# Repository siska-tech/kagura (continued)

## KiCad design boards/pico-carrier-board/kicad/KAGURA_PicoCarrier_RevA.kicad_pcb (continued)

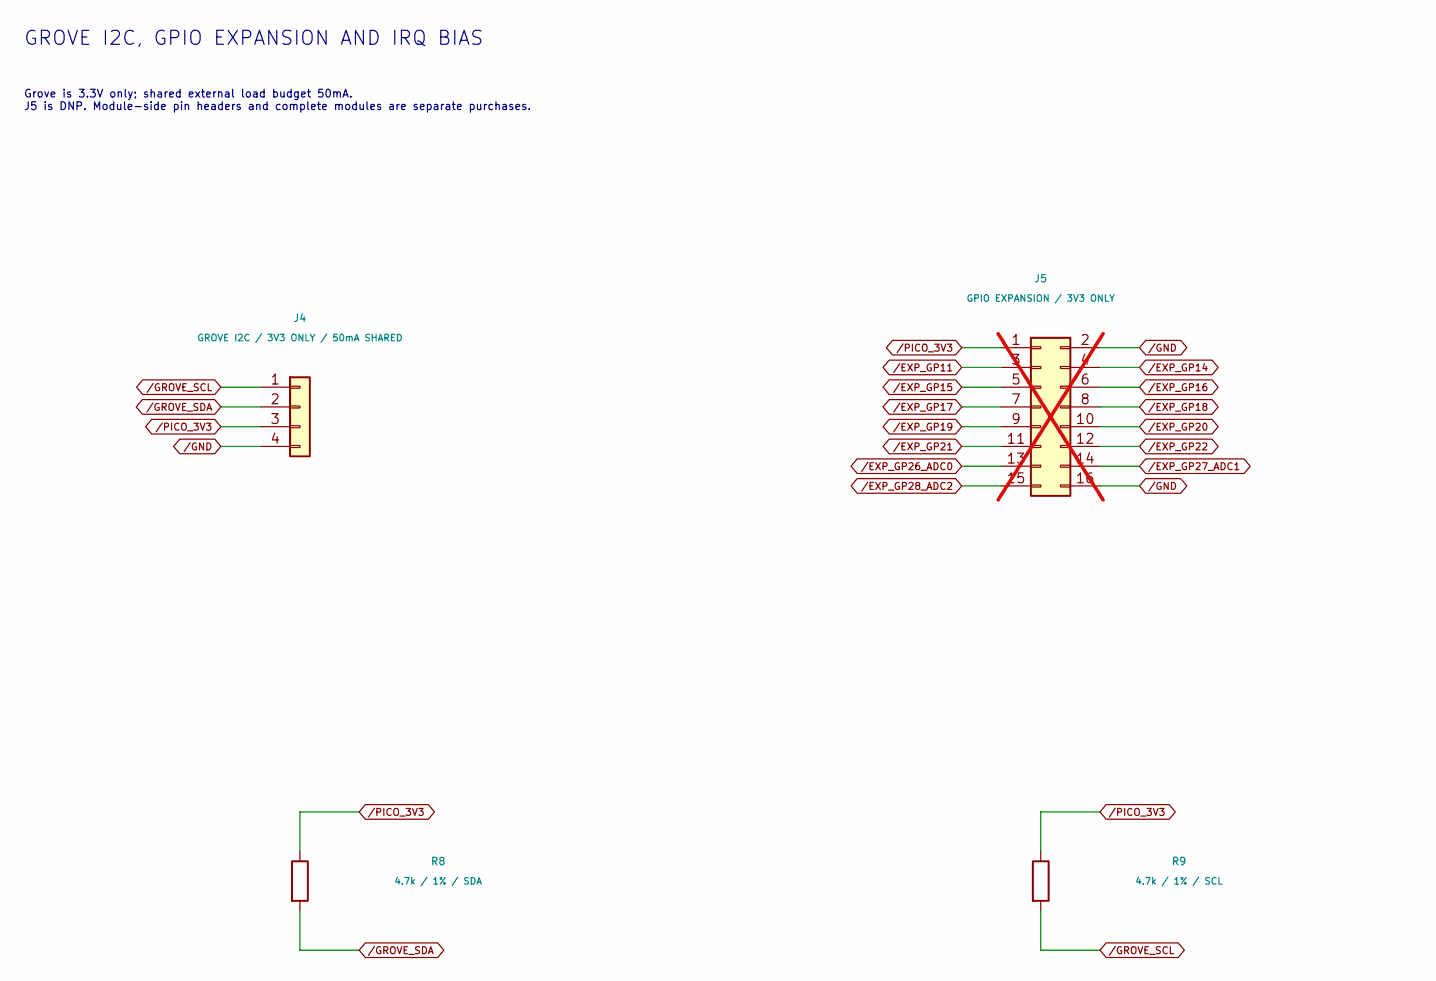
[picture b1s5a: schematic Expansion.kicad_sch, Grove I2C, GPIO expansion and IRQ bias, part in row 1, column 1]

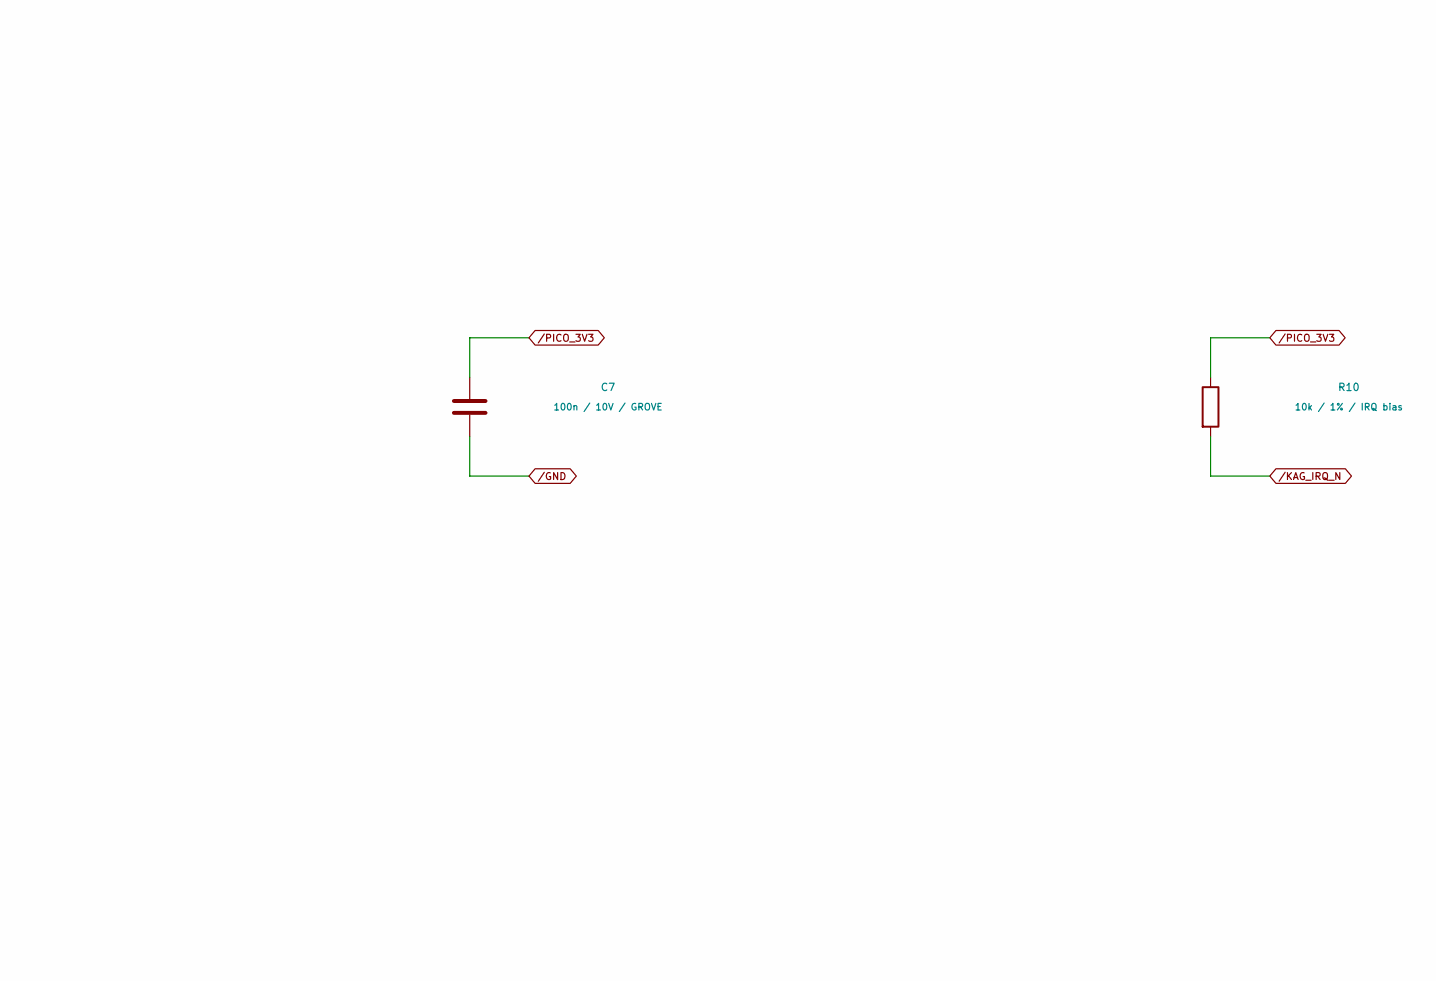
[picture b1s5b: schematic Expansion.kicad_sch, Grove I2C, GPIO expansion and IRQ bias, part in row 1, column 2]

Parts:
C7: 100n / 10V / GROVE; C7
J4: GROVE I2C / 3V3 ONLY / 50mA SHARED; J4
J5: GPIO EXPANSION / 3V3 ONLY; J5; not fitted
R8: 4.7k / 1% / SDA; R8
R9: 4.7k / 1% / SCL; R9
R10: 10k / 1% / IRQ bias; R10

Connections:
/EXP_GP11: J5.3; also elsewhere on the board
/EXP_GP14: J5.4; also elsewhere on the board
/EXP_GP15: J5.5; also elsewhere on the board
/EXP_GP16: J5.6; also elsewhere on the board
/EXP_GP17: J5.7; also elsewhere on the board
/EXP_GP18: J5.8; also elsewhere on the board
/EXP_GP19: J5.9; also elsewhere on the board
/EXP_GP20: J5.10; also elsewhere on the board
/EXP_GP21: J5.11; also elsewhere on the board
/EXP_GP22: J5.12; also elsewhere on the board
/EXP_GP26_ADC0: J5.13; also elsewhere on the board
/EXP_GP27_ADC1: J5.14; also elsewhere on the board
/EXP_GP28_ADC2: J5.15; also elsewhere on the board
/GND: C7.2, J4.4, J5.2, J5.16; also elsewhere on the board
/GROVE_SCL: J4.1, R9.2; also elsewhere on the board
/GROVE_SDA: J4.2, R8.2; also elsewhere on the board
/KAG_IRQ_N: R10.2; also elsewhere on the board
/PICO_3V3: C7.1, J4.3, J5.1, R8.1, R9.1, R10.1; also elsewhere on the board

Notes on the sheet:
GROVE I2C, GPIO EXPANSION AND IRQ BIAS
Grove is 3.3V only; shared external load budget 50mA. J5 is DNP. Module-side pin headers and complete modules are separate purchases.

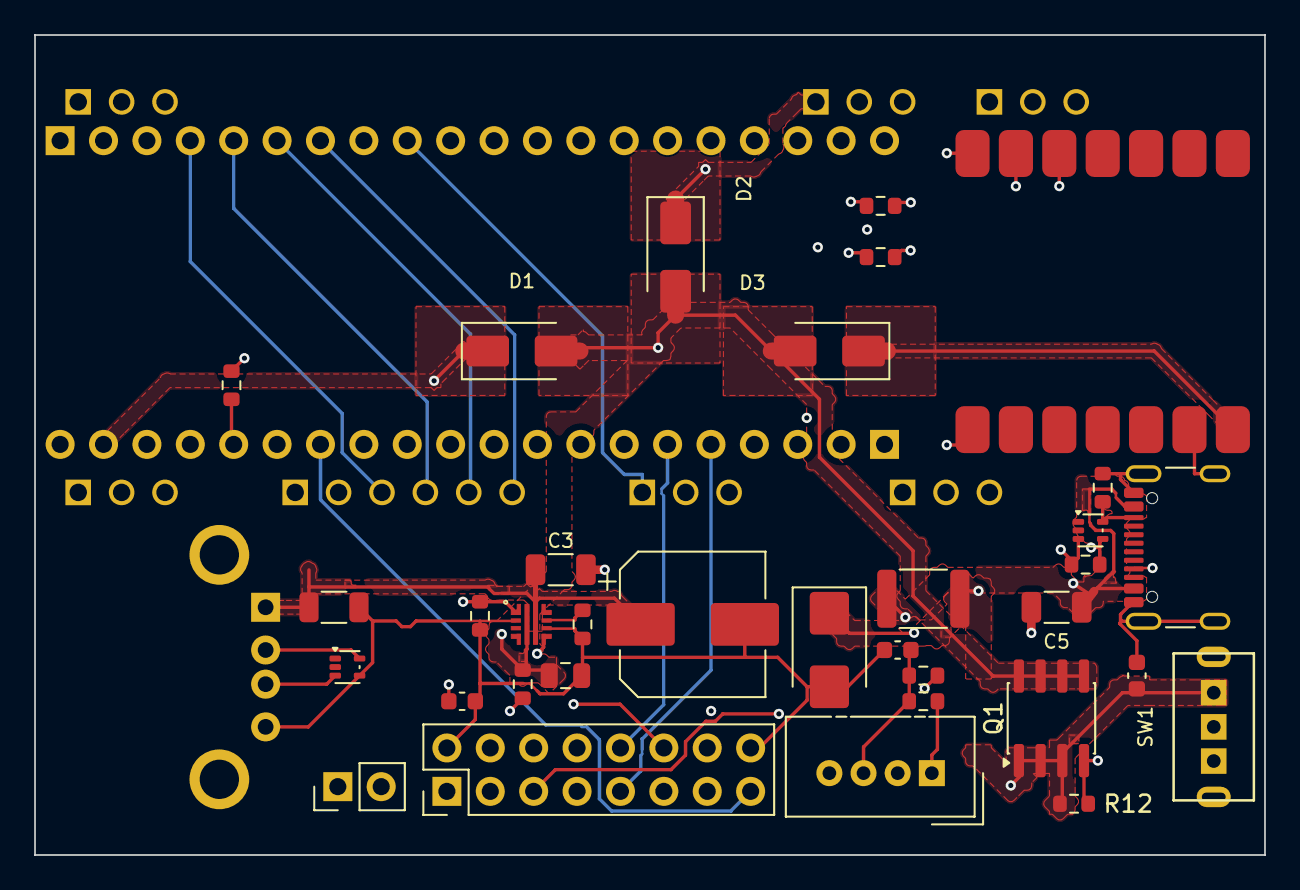
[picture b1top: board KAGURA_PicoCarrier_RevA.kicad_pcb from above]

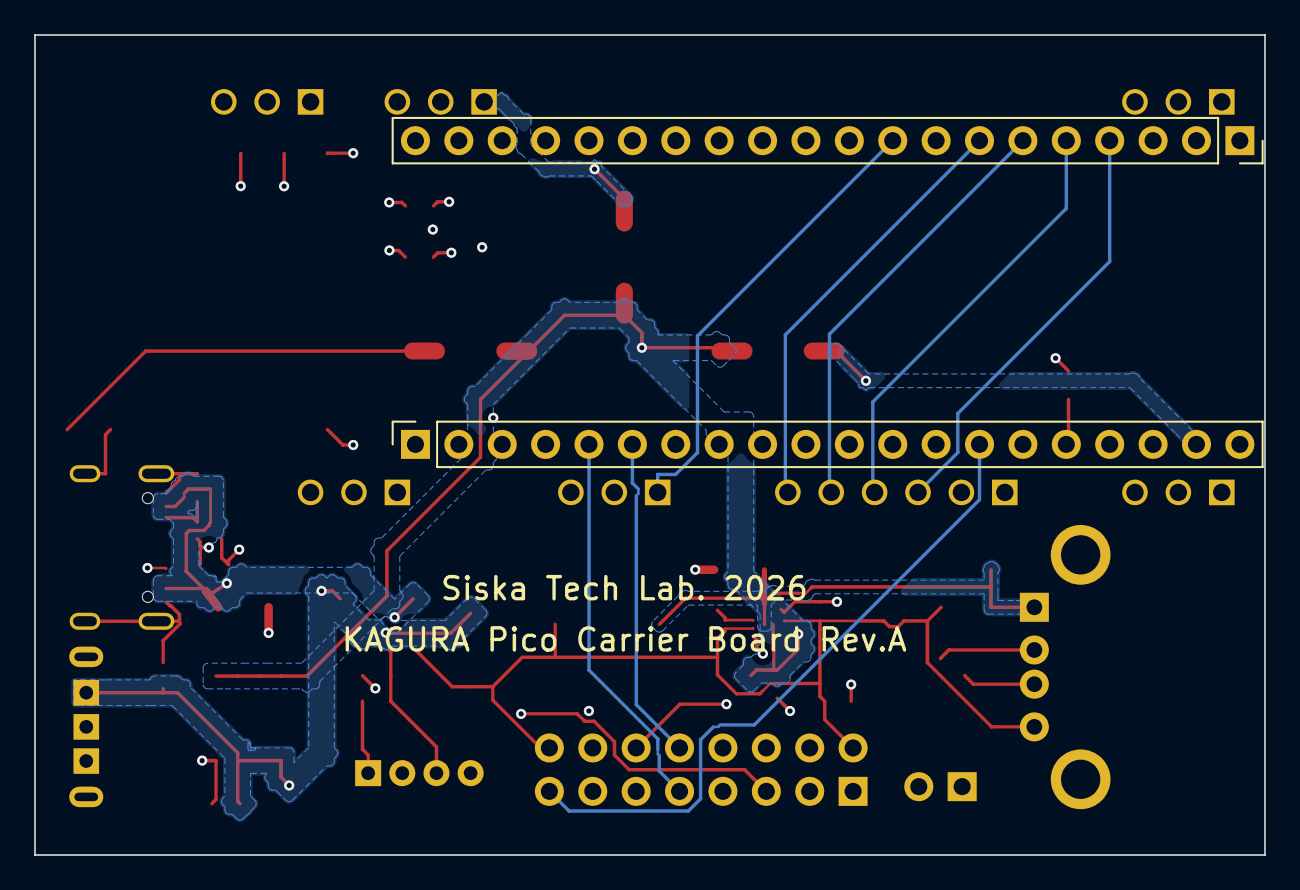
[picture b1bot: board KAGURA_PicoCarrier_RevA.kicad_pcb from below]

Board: 4 copper layers, 72.0 x 48.0 mm, 44 parts (2 on the bottom side), 46 nets.

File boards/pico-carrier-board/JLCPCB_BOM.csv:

Comment,Designator,Footprint,LCSC Part #
1u / 50V / X7R / 10%,C1,KAGURA_MANUAL:C1,C28323
4.7u / 50V / X7R / 10%,C3,KAGURA_BASIC:C_1206_3216Metric,C29823
220u / 10V / 20%,C4,KAGURA_MANUAL:C4,C401648
4.7u / 50V / X7R / 10%,C5,KAGURA_BASIC:C_1206_3216Metric,C29823
100n / 16V / X7R,C6,KAGURA_MANUAL:C6,C14663
100n / 10V / GROVE,C7,KAGURA_MANUAL:C7,C14663
4.7n / 50V / X7R / 10% / dVdt,C8,KAGURA_MANUAL:C8,C53987
SS34 / MDD / Basic / Pico,D1,KAGURA_BASIC:D_SMA,C8678
SS34 / MDD / Basic / Tang,D2,KAGURA_BASIC:D_SMA,C8678
SS34 / MDD / Basic / XIAO,D3,KAGURA_BASIC:D_SMA,C8678
SMBJ6.0CA / alternate / TRANSIENT ONLY,D4,KAGURA_MANUAL:D4,C19077561
MINISMDC260F/16-2 / alternate 2.6Ahold,F1,KAGURA_MANUAL:F1,C16490
AO4407A / prototype,Q1,SOIC-8_3.9x4.9mm_P1.27mm,C16072
22 / 1%,R1,KAGURA_MANUAL:R1,C23345
10k / 1% / IRQ bias,R10,KAGURA_MANUAL:R10,C25804
100k / 1% / EN feed,R11,KAGURA_MANUAL:R11,C25803
100k / 1% / gate pull-up,R12,R_0603_1608Metric,C25803
22 / 1%,R2,KAGURA_MANUAL:R2,C23345
5.36k / 1% / ILM,R3,KAGURA_MANUAL:R3,C25973
100k / 1% / EN pulldown,R4,KAGURA_MANUAL:R4,C25803
1k / 1% / 0.25W,R5,KAGURA_MANUAL:R5,C4410
5.1k / 1% / CC1 Rd,R6,KAGURA_MANUAL:R6,C23186
5.1k / 1% / CC2 Rd,R7,KAGURA_MANUAL:R7,C23186
4.7k / 1% / SDA,R8,KAGURA_MANUAL:R8,C23162
4.7k / 1% / SCL,R9,KAGURA_MANUAL:R9,C23162
TPS259470ARPWR / HOST LIMIT+RCB,U2,KAGURA_MANUAL:U2,C3662799
TPD2E2U06DRLR,U4,KAGURA_MANUAL:U4,C1972959
TPD2E2U06DRLR / CC ESD,U5,KAGURA_MANUAL:U5,C1972959
